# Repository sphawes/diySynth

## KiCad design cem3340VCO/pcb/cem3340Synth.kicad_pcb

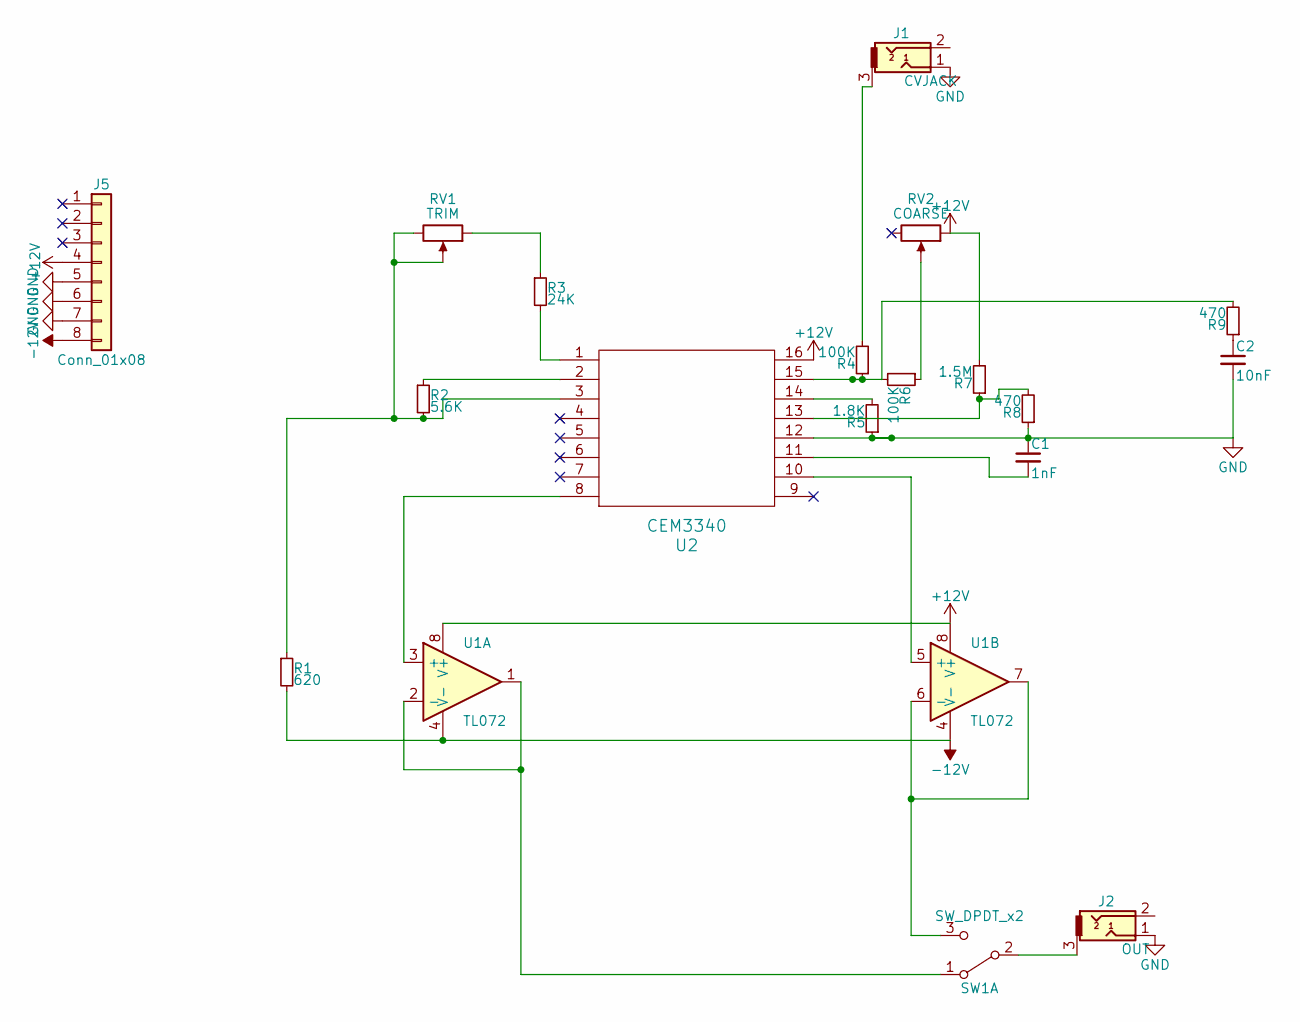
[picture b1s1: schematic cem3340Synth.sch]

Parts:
C1: 1nF; C_0805_HandSoldering
C2: 10nF; C_0805_HandSoldering
J1: CVJACK; Pin_Header_Straight_1x03_Pitch2.54mm
J2: OUT; Pin_Header_Straight_1x03_Pitch2.54mm
J5: Conn_01x08; Pin_Header_Straight_1x08_Pitch2.54mm
R1: 620; R_0805_HandSoldering
R2: 5.6K; R_0805_HandSoldering
R3: 24K; R_0805_HandSoldering
R4, R6: 100K; R_0805_HandSoldering
R5: 1.8K; R_Axial_DIN0204_L3.6mm_D1.6mm_P7.62mm_Horizontal
R7: 1.5M; R_Axial_DIN0204_L3.6mm_D1.6mm_P7.62mm_Horizontal
R8, R9: 470; R_0805_HandSoldering
RV1: TRIM; Pin_Header_Straight_1x03_Pitch2.54mm
RV2: COARSE; Pin_Header_Straight_1x03_Pitch2.54mm
SW1: SW_DPDT_x2; Pin_Header_Straight_1x03_Pitch2.54mm
U1: TL072; DIP-8_W7.62mm_Socket_LongPads
U2: CEM3340; DIP-16_W7.62mm_Socket_LongPads

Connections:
+12V: J5.4, R7.2, RV2.1, U1.8 (V+), U2.16
-12V: J5.8, R1.2, U1.4 (V-)
GND: C1.1, C2.2, J1.1, J2.1, J5.5, J5.6, J5.7, R5.1, R8.1, U2.12
unnamed: C1.2, U2.11
unnamed: C2.1, R9.1
unnamed: J1.3, R4.2
unnamed: J2.3, SW1.2 (B)
unnamed: R1.1, R2.2, RV1.2, RV1.3, U2.3
unnamed: R2.1, U2.2
unnamed: R3.1, RV1.1
unnamed: R3.2, U2.1
unnamed: R4.1, R6.2, R9.2, U2.15
unnamed: R5.2, U2.14
unnamed: R6.1, RV2.2
unnamed: R7.1, R8.2, U2.13
unnamed: SW1.1 (A), U1.1, U1.2 (-)
unnamed: SW1.3 (C), U1.6 (-), U1.7
unnamed: U1.3 (+), U2.8
unnamed: U1.5 (+), U2.10

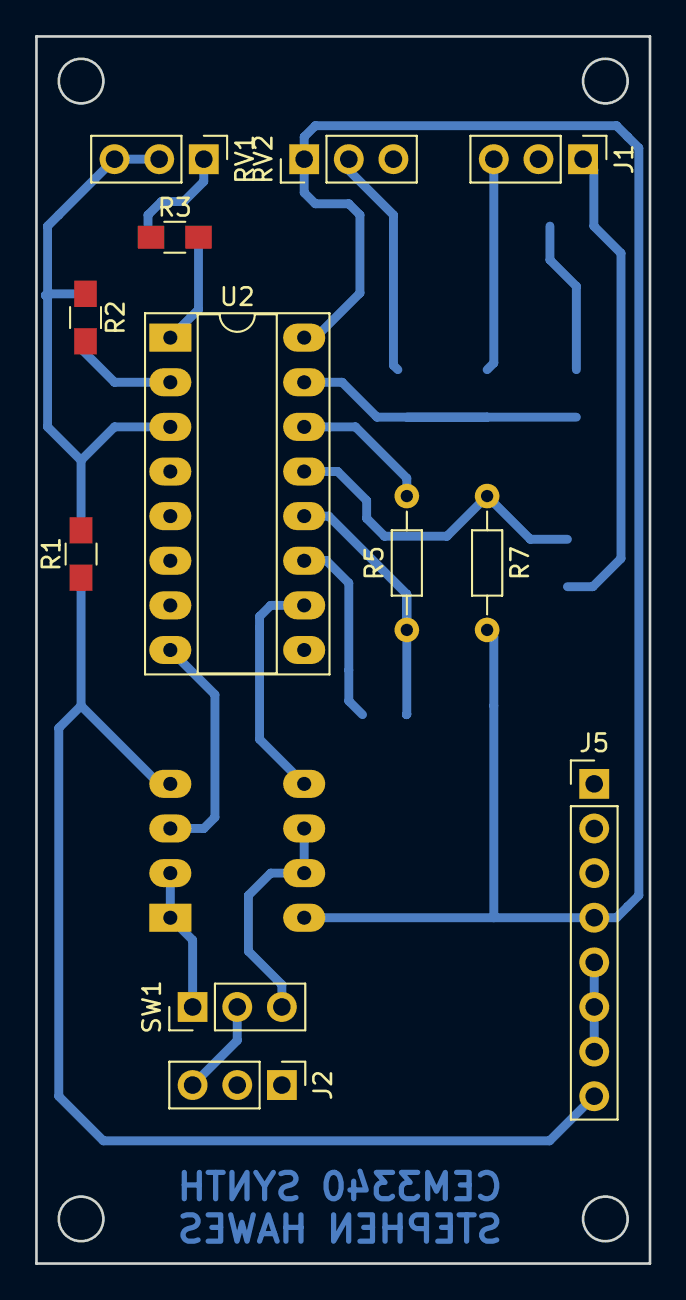
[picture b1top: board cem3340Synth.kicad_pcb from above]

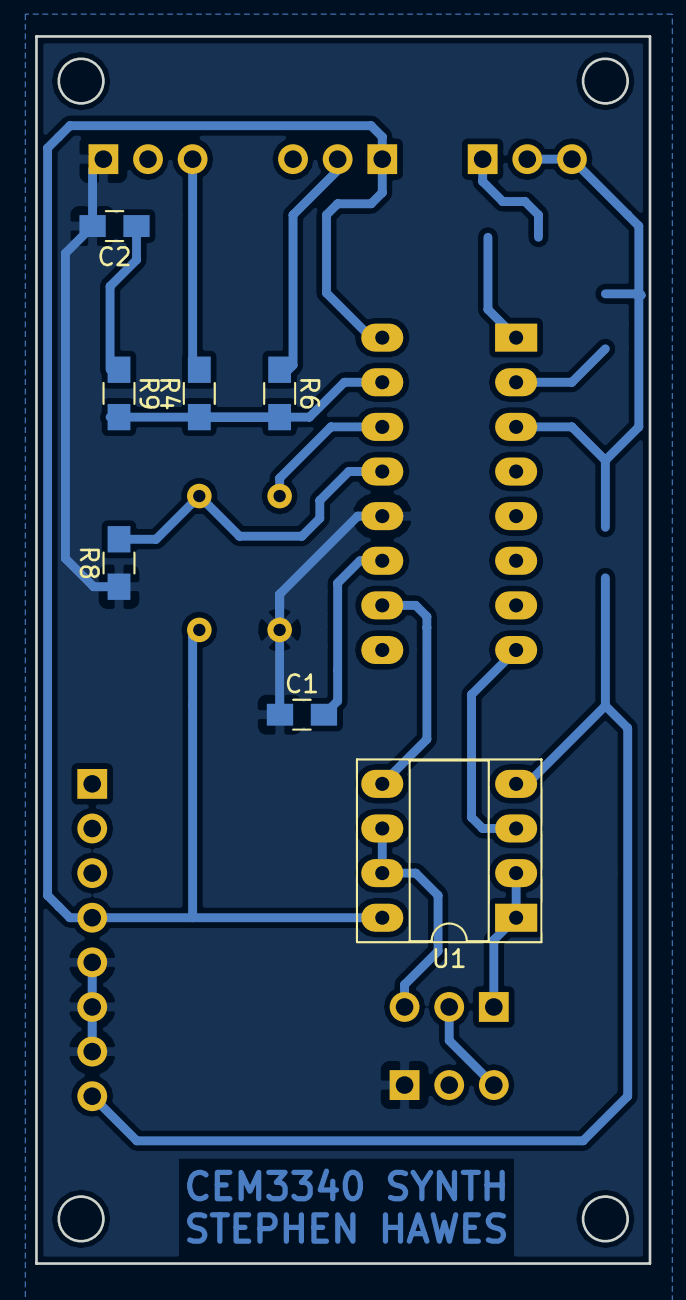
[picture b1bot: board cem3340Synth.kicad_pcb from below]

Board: 2 copper layers, 34.9 x 69.8 mm, 19 parts (7 on the bottom side), 19 nets.

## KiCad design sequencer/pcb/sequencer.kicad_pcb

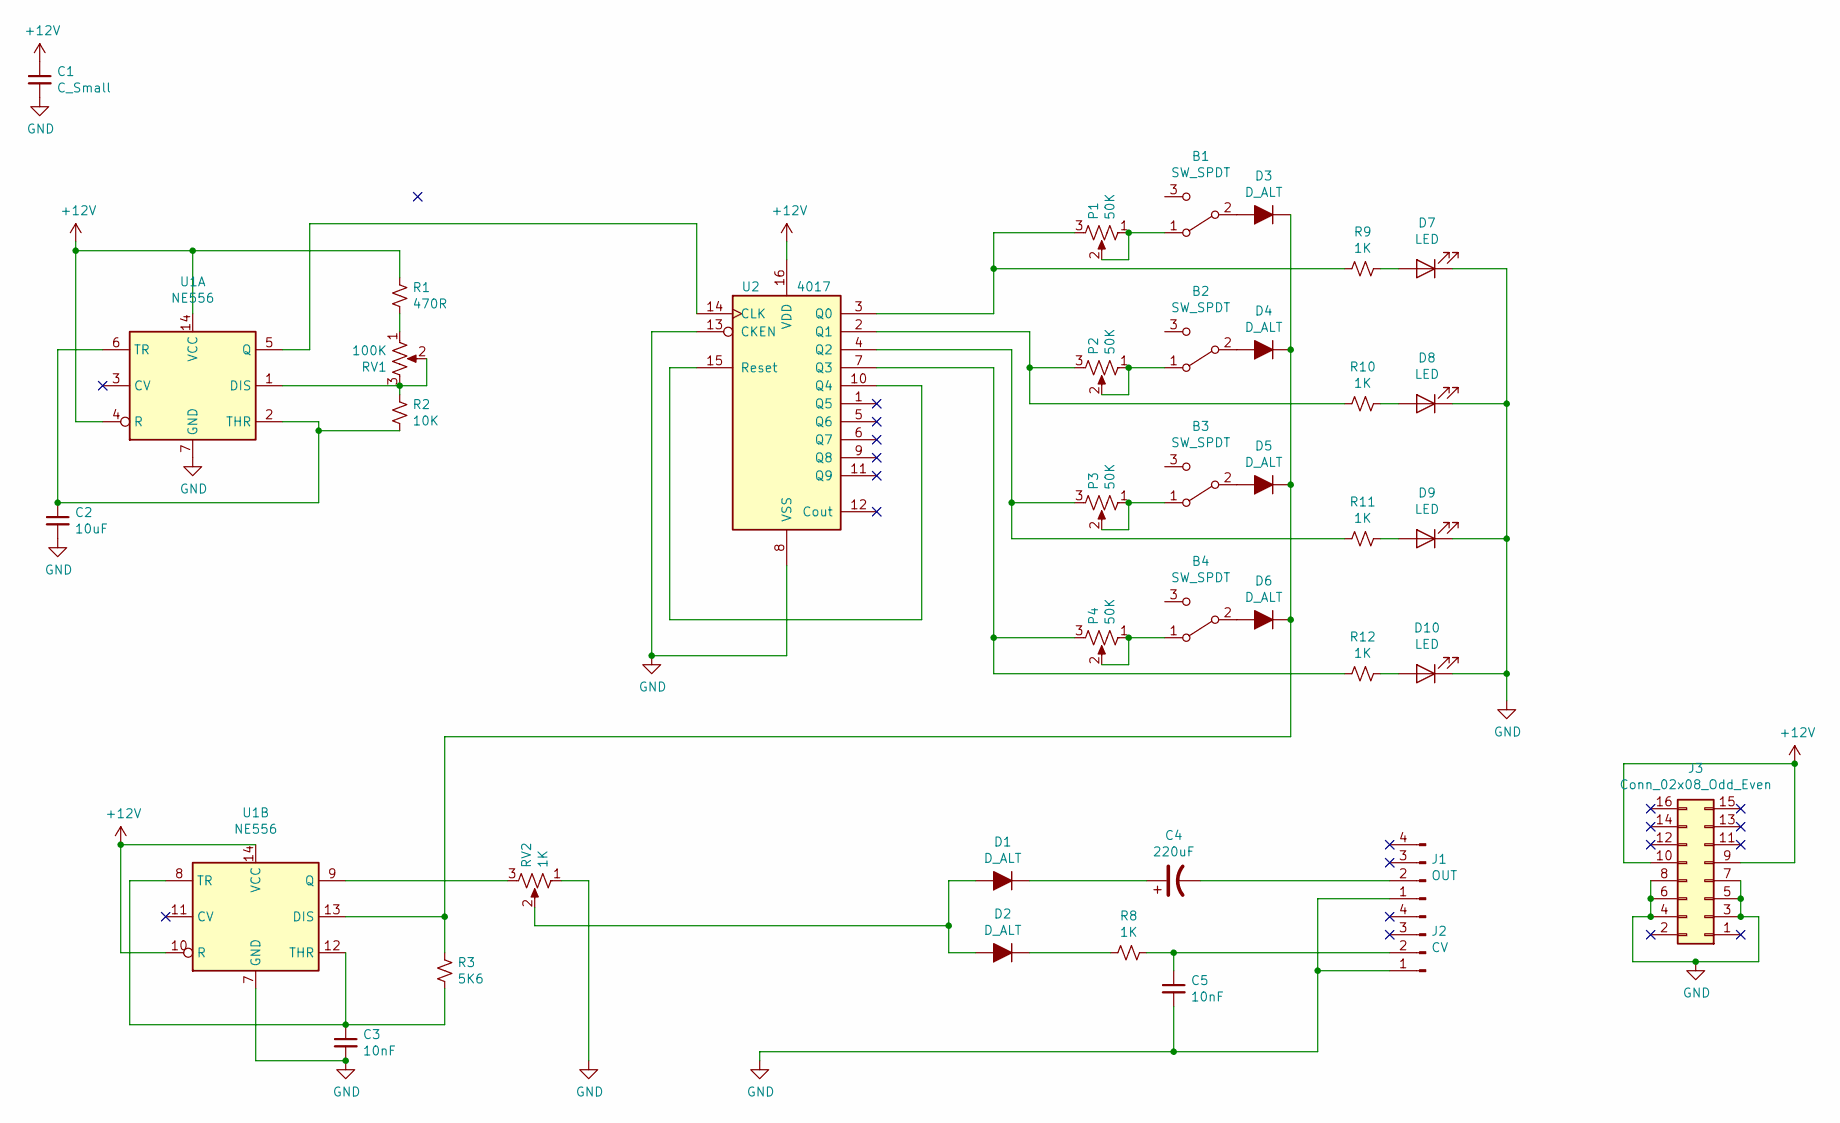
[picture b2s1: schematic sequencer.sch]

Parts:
B1, B2, B3, B4: SW_SPDT; PVA1_EE_H2_1.2NV2
C1: C_Small; C_0805_2012Metric_Pad1.15x1.40mm_HandSolder
C2: 10uF; C_0805_2012Metric_Pad1.15x1.40mm_HandSolder
C3, C5: 10nF; C_0805_2012Metric_Pad1.15x1.40mm_HandSolder
C4: 220uF; C_0805_2012Metric_Pad1.15x1.40mm_HandSolder
D1, D2, D3, D4, D5, D6: D_ALT; D_SOD-523
D7, D8, D9, D10: LED; LED_D5.0mm
J1: OUT; molex_stereo_3.5mm_jack
J2: CV; molex_stereo_3.5mm_jack
J3: Conn_02x08_Odd_Even; PinSocket_2x08_P2.54mm_Vertical
P1, P2, P3, P4: 50K; slidePot
R1: 470R; R_0805_2012Metric_Pad1.15x1.40mm_HandSolder
R2: 10K; R_0805_2012Metric_Pad1.15x1.40mm_HandSolder
R3: 5K6; R_0805_2012Metric_Pad1.15x1.40mm_HandSolder
R8, R9, R10, R11, R12: 1K; R_0805_2012Metric_Pad1.15x1.40mm_HandSolder
RV1: 100K; Potentiometer_Bourns_PTV09A-1_Single_Vertical
RV2: 1K; Potentiometer_Bourns_PTV09A-1_Single_Vertical
U1: NE556; SOIC-14_3.9x8.7mm_P1.27mm
U2: 4017; SOIC-16_3.9x9.9mm_P1.27mm

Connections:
+12V: C1.1, J3.9, J3.10, R1.1, U1.4 (R), U1.10 (R), U1.14 (VCC), U2.16 (VDD)
GND: C1.2, C2.2, C3.2, C5.2, D7.1 (K), D8.1 (K), D9.1 (K), D10.1 (K), J1.1, J2.1, J3.3, J3.4, J3.5, J3.6, J3.7, J3.8, RV2.1, U1.7 (GND), U2.8 (VSS), U2.13 (CKEN)
unnamed: B1.1 (A), P1.1, P1.2
unnamed: B1.2 (B), D3.2 (A)
unnamed: B2.1 (A), P2.1, P2.2
unnamed: B2.2 (B), D4.2 (A)
unnamed: B3.1 (A), P3.1, P3.2
unnamed: B3.2 (B), D5.2 (A)
unnamed: B4.1 (A), P4.1, P4.2
unnamed: B4.2 (B), D6.2 (A)
unnamed: C2.1, R2.2, U1.2 (THR), U1.6 (TR)
unnamed: C3.1, R3.2, U1.8 (TR), U1.12 (THR)
unnamed: C4.1, D1.1 (K)
unnamed: C4.2, J1.2
unnamed: C5.1, J2.2, R8.1
unnamed: D1.2 (A), D2.2 (A), RV2.2
unnamed: D2.1 (K), R8.2
unnamed: D3.1 (K), D4.1 (K), D5.1 (K), D6.1 (K), R3.1, U1.13 (DIS)
unnamed: D7.2 (A), R9.1
unnamed: D8.2 (A), R10.1
unnamed: D9.2 (A), R11.1
unnamed: D10.2 (A), R12.1
unnamed: P1.3, R9.2, U2.3 (Q0)
unnamed: P2.3, R10.2, U2.2 (Q1)
unnamed: P3.3, R11.2, U2.4 (Q2)
unnamed: P4.3, R12.2, U2.7 (Q3)
unnamed: R1.2, RV1.1
unnamed: R2.1, RV1.2, RV1.3, U1.1 (DIS)
unnamed: RV2.3, U1.9 (Q)
unnamed: U1.5 (Q), U2.14 (CLK)
unnamed: U2.10 (Q4), U2.15 (Reset)

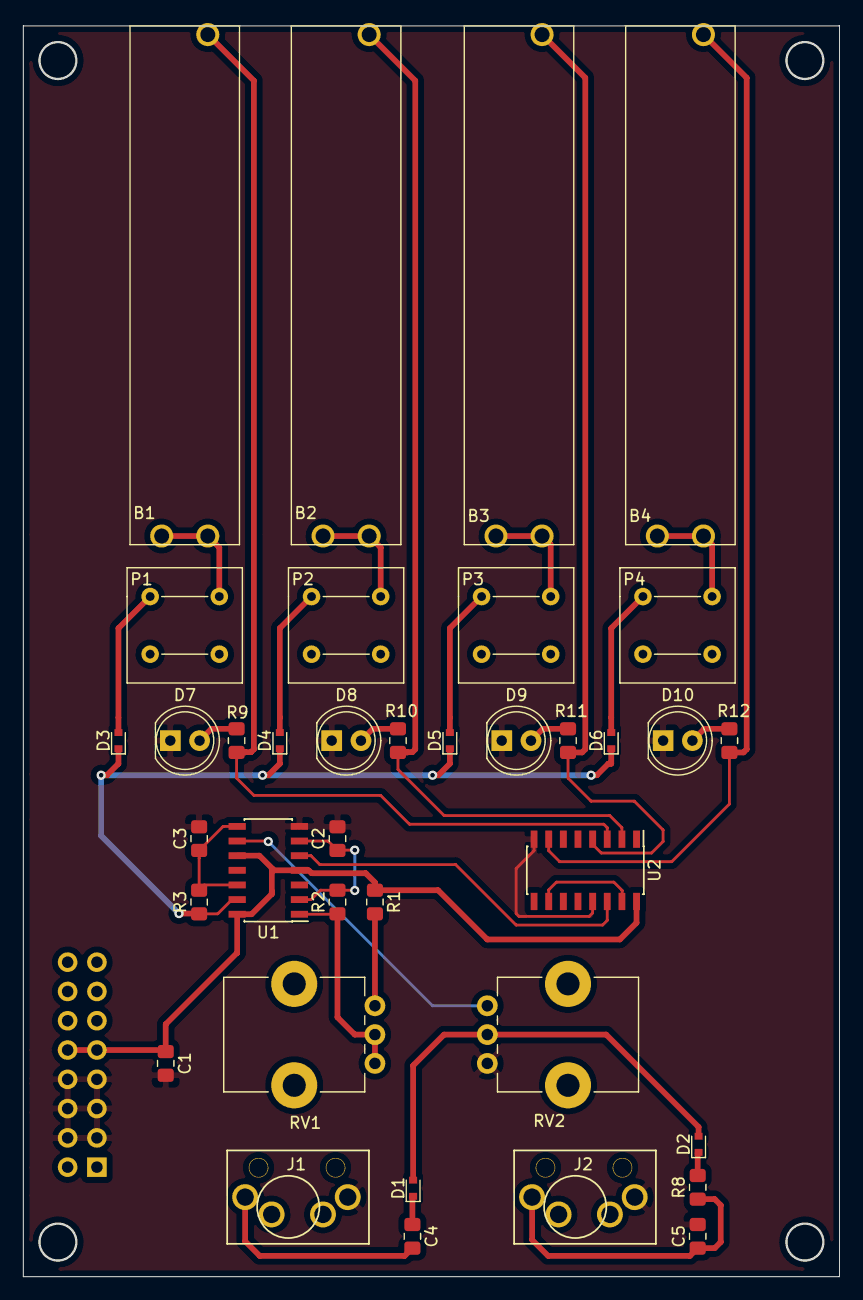
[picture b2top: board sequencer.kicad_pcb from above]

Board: 2 copper layers, 70.7 x 108.4 mm, 38 parts (1 on the bottom side), 31 nets.
